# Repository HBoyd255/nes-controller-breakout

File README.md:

# NES Controller Breakout Board

<!-- Harry Boyd - hboyd255@gmail.com - 16/04/2024 -->

This is a simple breakout board for the NES controller.

That I have made a
[KiCad library](https://github.com/HBoyd255/nes-controller-port) for the NES
port, and the port is available on
[zedlabz.com](https://www.zedlabz.com/products/controller-connector-port-for-nintendo-nes-console-7-pin-90-degree-replacement-2-pack-black-zedlabz?_pos=8&_sid=b3d25e834&_ss=r).

The reason I made this board is for debugging and testing. The NES controller is
beautifully simple, in that it contains a single 4021 shift register. This makes
it compatible with pretty much any microcontroller that has at least 3 spare
GPIO pins.

## Logic Lab

This board is part of a lab that I am creating for the York Engineering Society.
The lab is designed to give insight into how 4000 series logic chips work, and
despite their age, how they are still useful today.

## Fabrication

To fabricate this board, zip the contents of the `gerber` folder and upload them to your chosen PCB manufacturer. I would recommend using JLCPCB.

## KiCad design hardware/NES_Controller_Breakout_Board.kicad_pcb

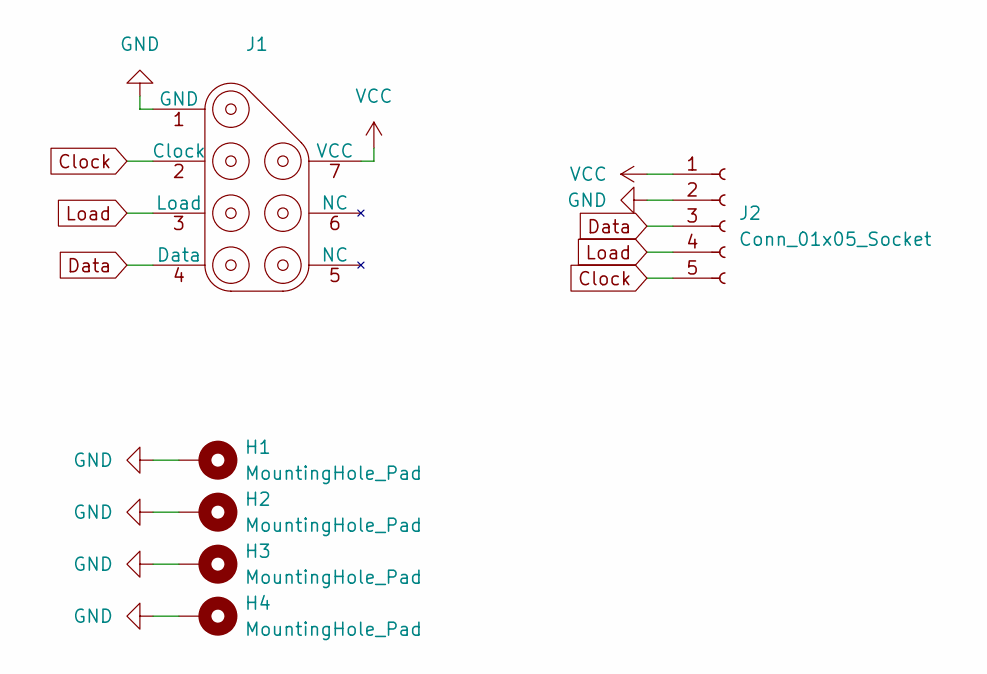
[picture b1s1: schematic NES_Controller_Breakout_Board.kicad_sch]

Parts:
H1, H2, H3, H4: MountingHole_Pad; MountingHole_2.7mm_M2.5_Pad
J1: NES_Controller_Port
J2: Conn_01x05_Socket; PinHeader_1x05_P2.54mm_Horizontal

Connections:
Clock: J1.2 (Clock), J2.5
Data: J1.4 (Data), J2.3
GND: H1.1, H2.1, H3.1, H4.1, J1.1 (GND), J2.2
Load: J1.3 (Load), J2.4
VCC: J1.7 (VCC), J2.1

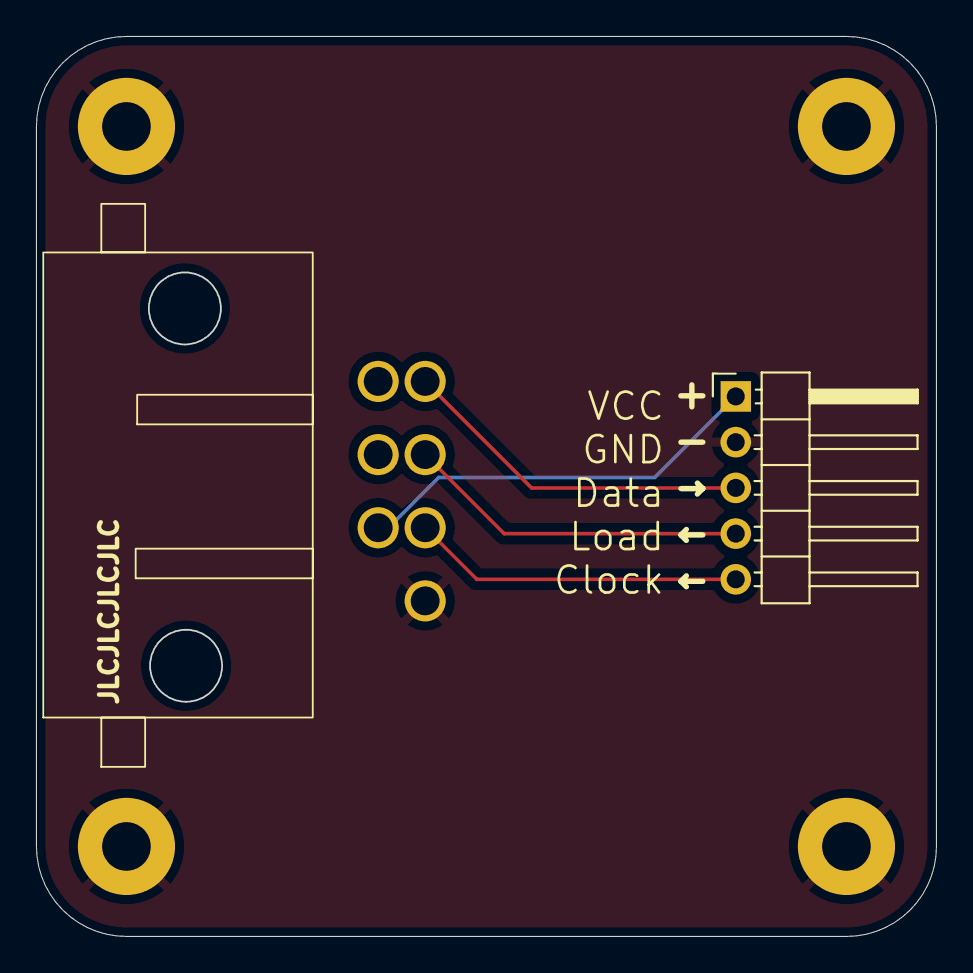
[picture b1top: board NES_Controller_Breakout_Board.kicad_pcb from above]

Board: 2 copper layers, 49.9 x 50.0 mm, 6 parts (0 on the bottom side), 5 nets.

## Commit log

2024-04-16 Added README.md and LICENSE
2024-04-16 Created the schematic, and layed out the components
2024-04-16 Routed PCB
2024-04-16 Renamed Project
2024-04-16 Finished design
2024-04-18 Updated output path
2024-04-18 Uploaded production files
2024-04-18 added image to README.md
2024-05-06 Fixed order of Start and Select
2024-05-22 Scaled text up
2024-05-22 Added 3D viewport
